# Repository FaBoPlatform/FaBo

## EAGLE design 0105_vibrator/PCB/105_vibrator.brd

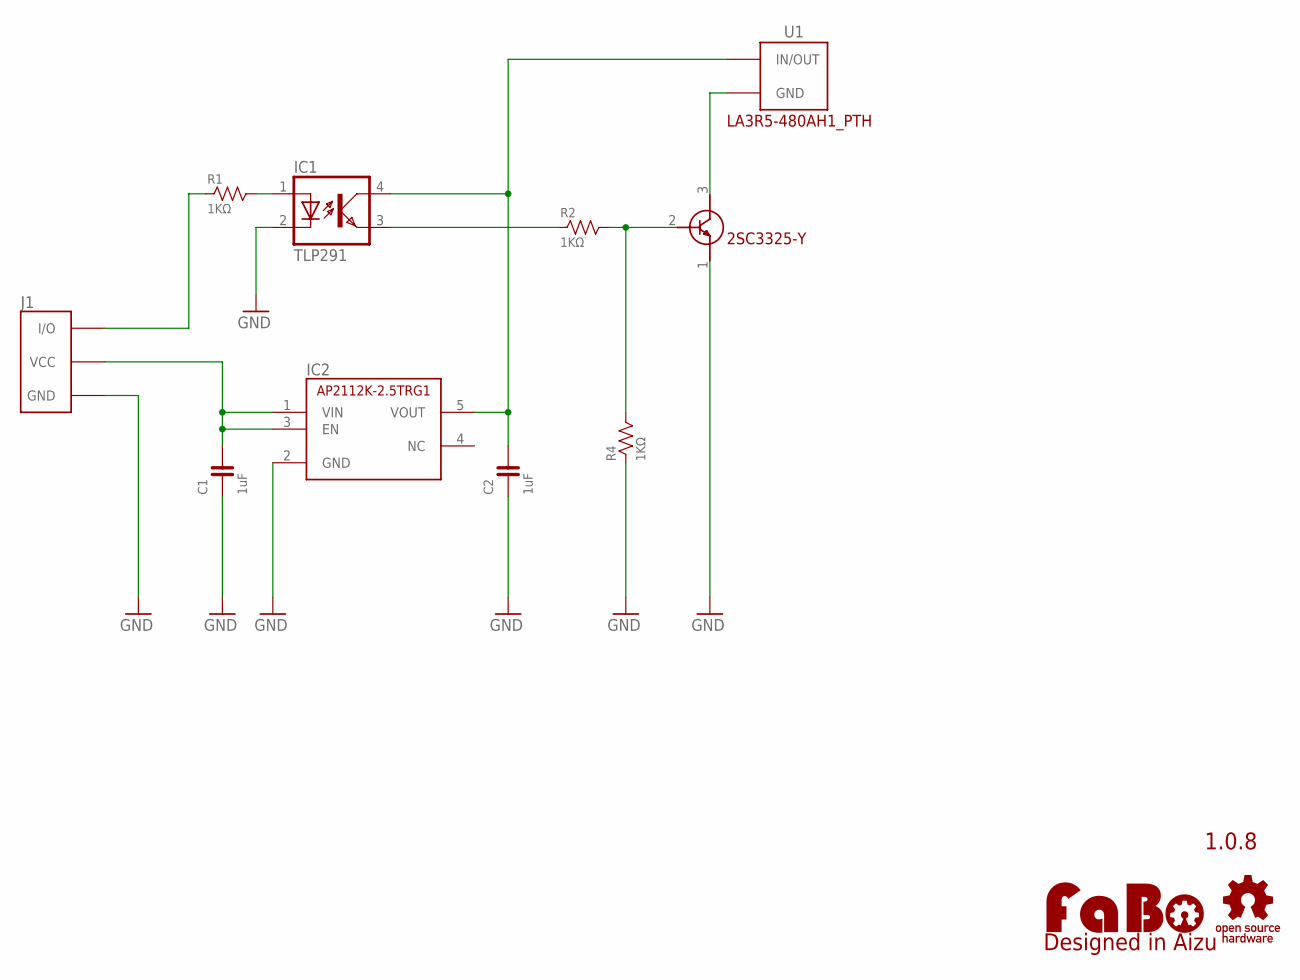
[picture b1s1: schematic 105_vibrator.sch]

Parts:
C1, C2: 1uF; 0603
IC1: TLP291; MINI-FLAT-4
IC2: AP2112-2.5; SOT-23-5
J1: FABO_BRICK_3PIN
LOGO1: LOGO_FABO-M; LOGO_FABO_M
R1, R2, R4: 1KΩ; 0603
TR1: 2SC3325-Y; SC-59
U1: VIBRATOR; LA3R5-480AH1_PTH
U$2: LOGO_OSHW-M_BOTTOM; LOGO_OSHW_M_BOTTOM

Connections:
GND: C1.1, C2.1, IC1.2 (C), IC2.2 (GND), J1.GND, R4.1, TR1.1 (E)
unnamed: J1.I/O, R1.1
unnamed: IC1.1 (A), R1.2
unnamed: IC1.3 (EMIT), R2.1
unnamed: C2.2, IC1.4 (COL), IC2.5 (VOUT), U1.P$1 (IN/OUT)
unnamed: TR1.3 (C), U1.P$2 (GND)
unnamed: R2.2, R4.2, TR1.2 (B)
VCC: C1.2, IC2.1 (VIN), IC2.3 (EN), J1.VCC

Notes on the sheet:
1.0.8
LA3R5-480AH1_PTH

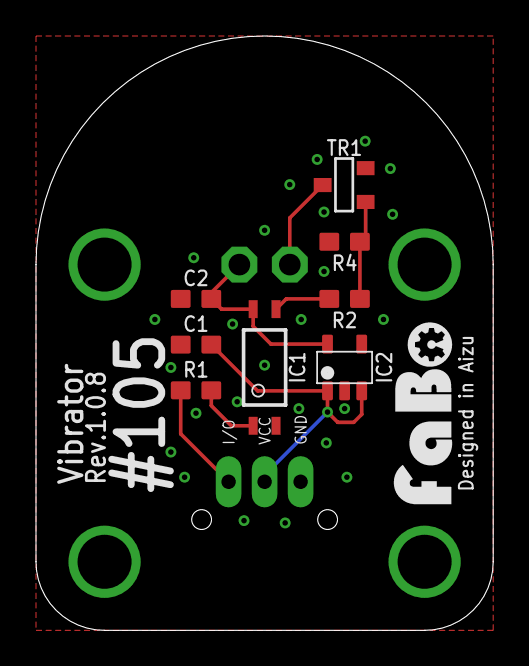
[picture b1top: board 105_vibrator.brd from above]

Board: 2 copper layers, 25.4 x 33.0 mm, 12 parts (0 on the bottom side), 8 nets.

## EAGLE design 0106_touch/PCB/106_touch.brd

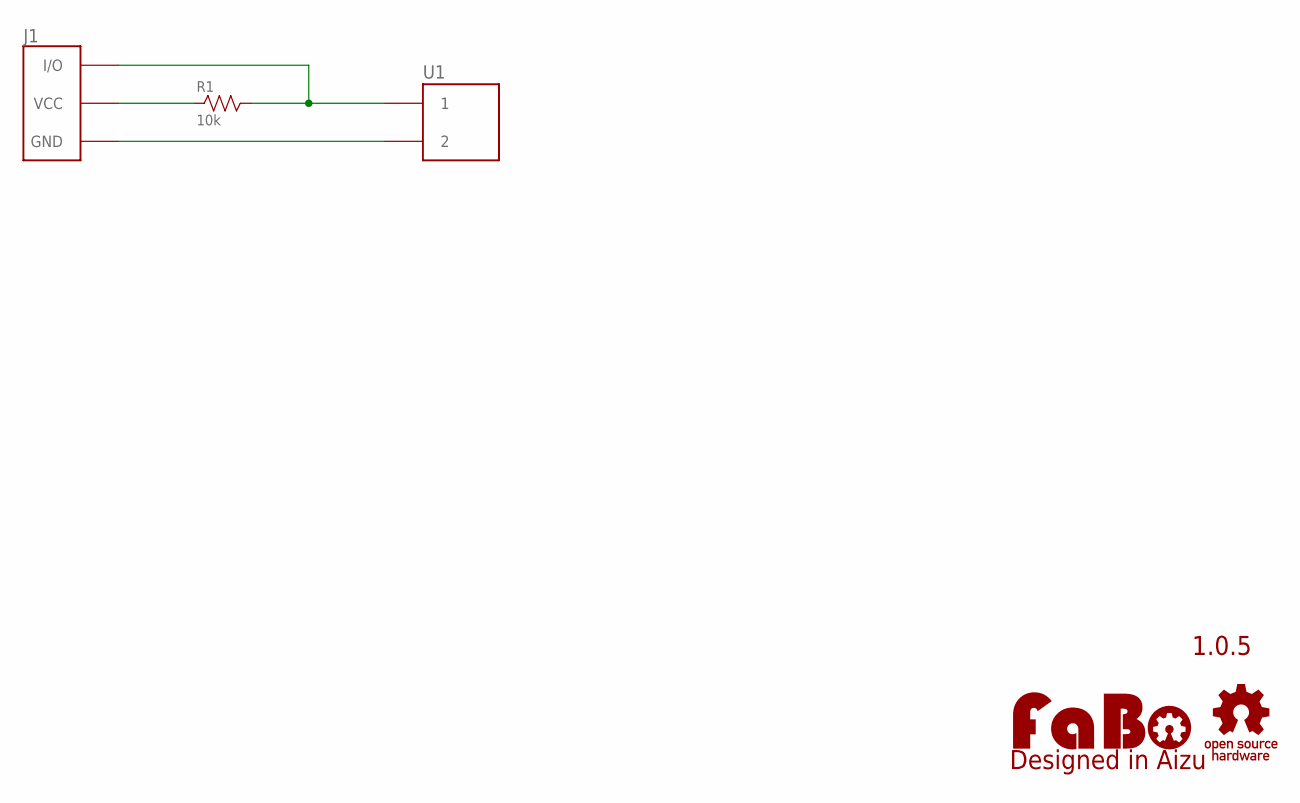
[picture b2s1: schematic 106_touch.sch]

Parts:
J1: FABO_BRICK_3PIN
LOGO1: LOGO_FABO-M; LOGO_FABO_M
R1: 10k; AXL-REGULAR
U1: FSR402-SHORT
U$2: LOGO_OSHW-M_BOTTOM; LOGO_OSHW_M_BOTTOM

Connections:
GND: J1.GND, U1.P$2 (2)
unnamed: J1.I/O, R1.2, U1.P$1 (1)
unnamed: J1.VCC, R1.1

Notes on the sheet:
1.0.5

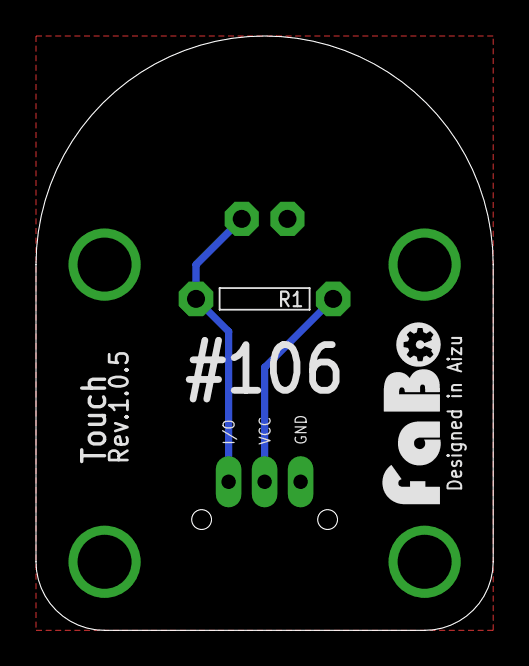
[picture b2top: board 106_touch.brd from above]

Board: 2 copper layers, 25.4 x 33.0 mm, 5 parts (0 on the bottom side), 3 nets.

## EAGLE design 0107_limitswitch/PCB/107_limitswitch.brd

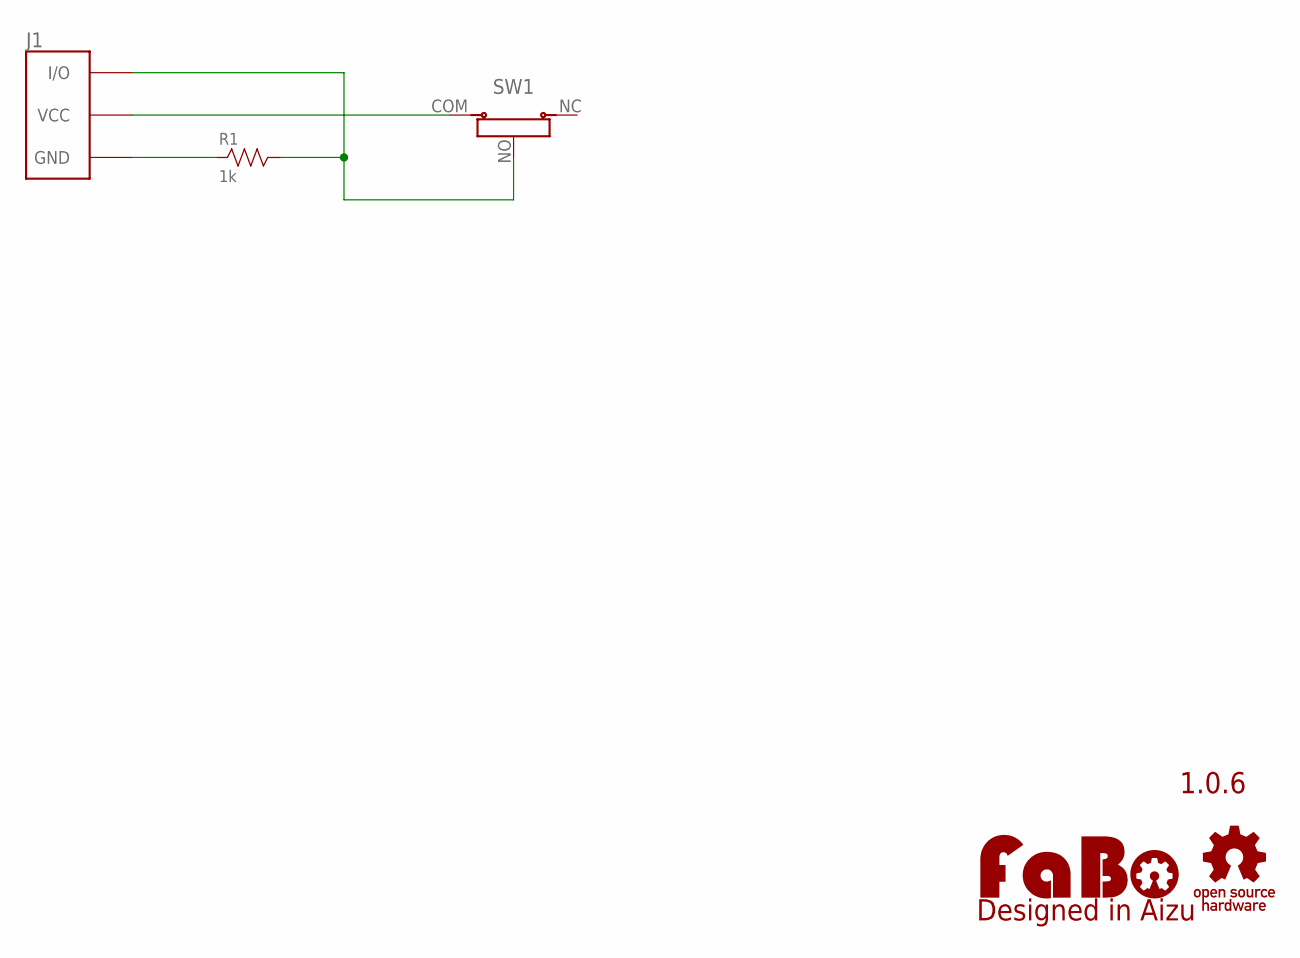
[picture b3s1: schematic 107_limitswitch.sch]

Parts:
J1: FABO_BRICK_3PIN
LOGO1: LOGO_FABO-M; LOGO_FABO_M
R1: 1k; AXL-REGULAR
SW1: LIMIT-SWITCH
U$2: LOGO_OSHW-M_BOTTOM; LOGO_OSHW_M_BOTTOM

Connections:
GND: J1.GND, R1.1
unnamed: J1.VCC, SW1.COM (VCC)
unnamed: J1.I/O, R1.2, SW1.NO

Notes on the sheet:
1.0.6

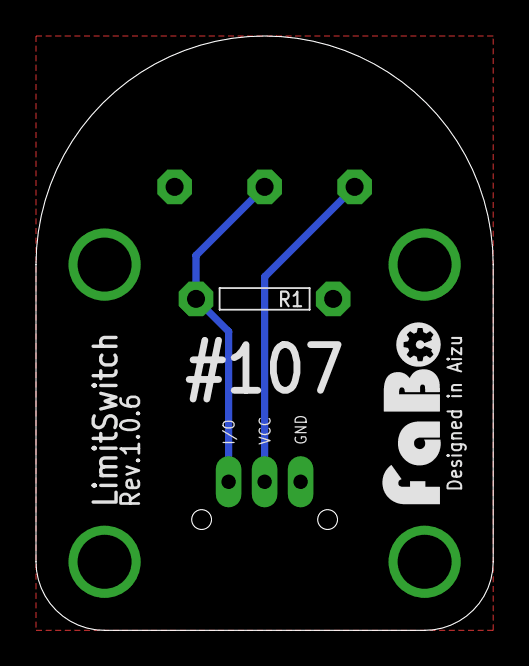
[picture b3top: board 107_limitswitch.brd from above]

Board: 2 copper layers, 25.4 x 33.0 mm, 5 parts (0 on the bottom side), 3 nets.

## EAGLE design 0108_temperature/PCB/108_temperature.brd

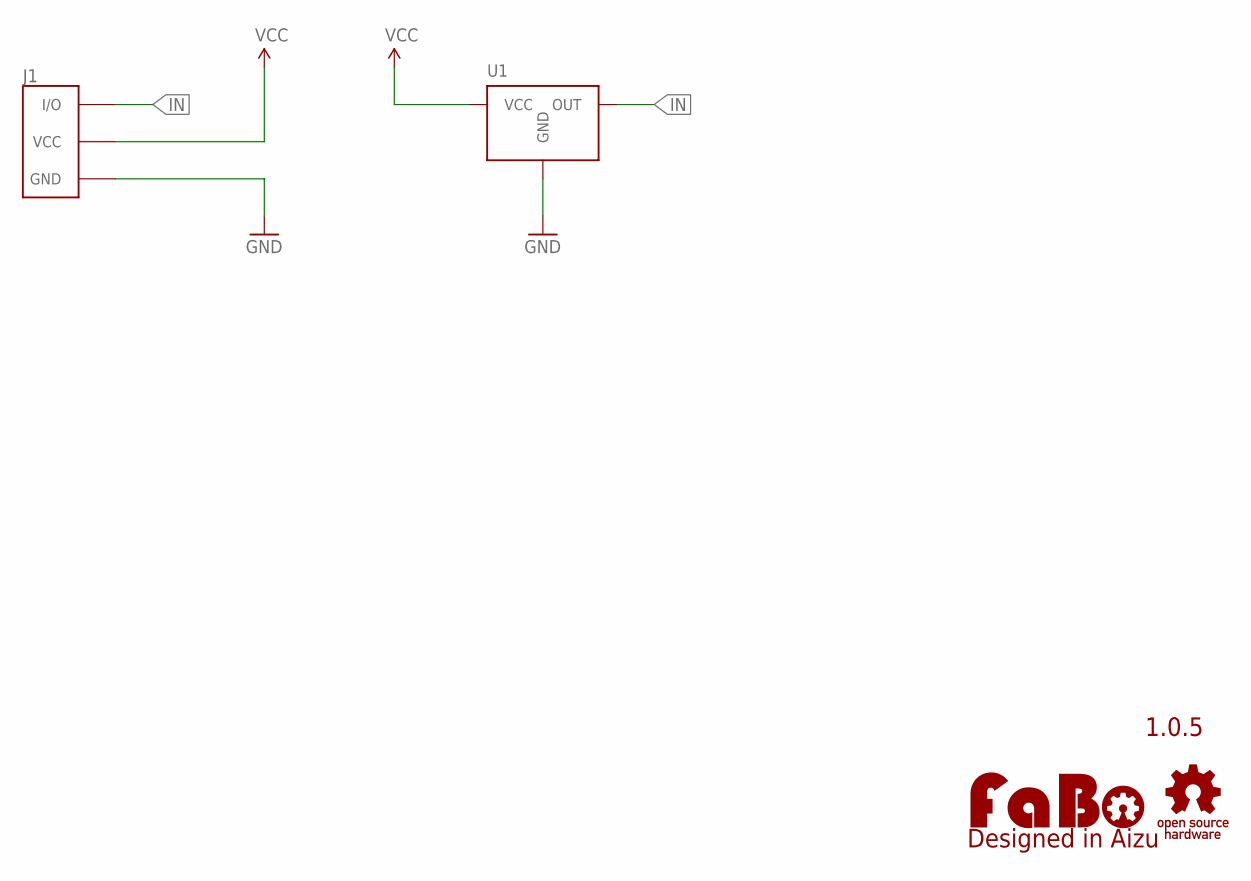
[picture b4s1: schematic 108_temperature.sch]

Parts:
J1: FABO_BRICK_3PIN
LOGO1: LOGO_FABO-M; LOGO_FABO_M
U1: LM61CIZ-TO-92; LM60-TO-92
U$2: LOGO_OSHW-M_BOTTOM; LOGO_OSHW_M_BOTTOM

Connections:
GND: J1.GND, U1.GND
IN: J1.I/O, U1.OUT
VCC: J1.VCC, U1.VCC

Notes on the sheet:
1.0.5

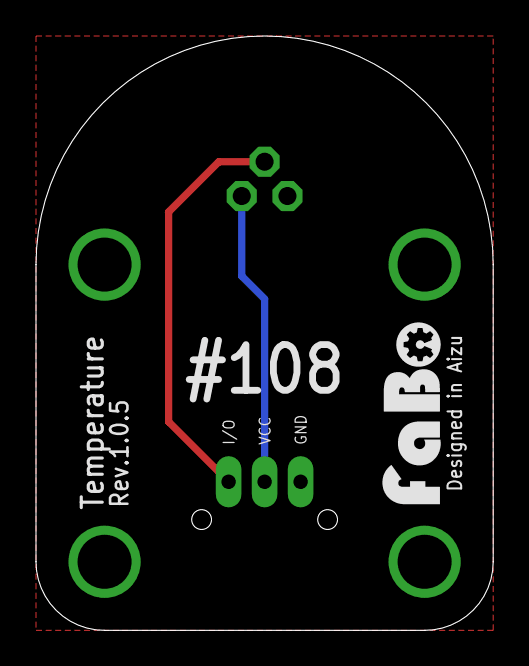
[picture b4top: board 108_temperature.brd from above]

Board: 2 copper layers, 25.4 x 33.0 mm, 4 parts (0 on the bottom side), 3 nets.

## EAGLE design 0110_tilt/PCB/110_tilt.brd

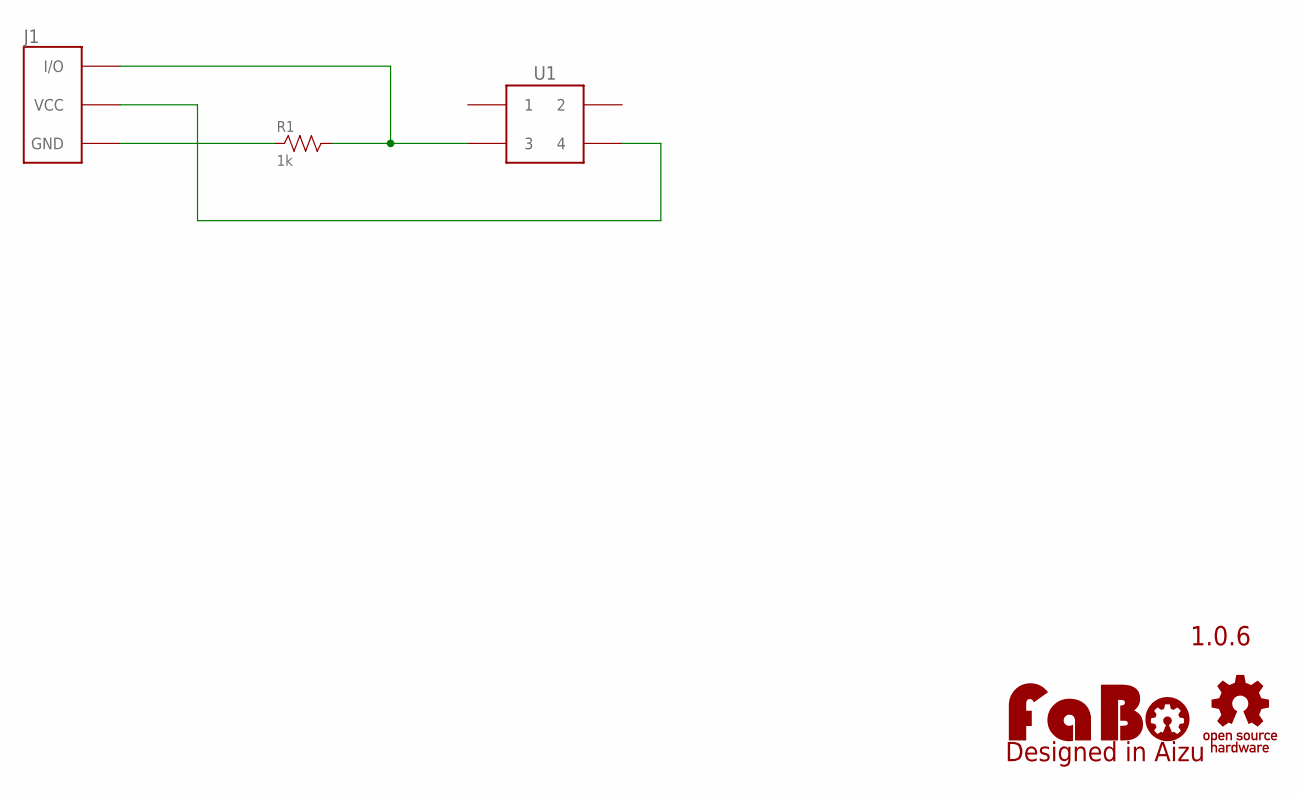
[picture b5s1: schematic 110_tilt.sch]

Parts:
J1: FABO_BRICK_3PIN
LOGO1: LOGO_FABO-M; LOGO_FABO_M
R1: 1k; AXL-REGULAR
U1: TILT; RBS040200
U$2: LOGO_OSHW-M_BOTTOM; LOGO_OSHW_M_BOTTOM

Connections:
GND: J1.GND, R1.1
unnamed: J1.I/O, R1.2, U1.3
unnamed: J1.VCC, U1.4

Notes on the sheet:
1.0.6

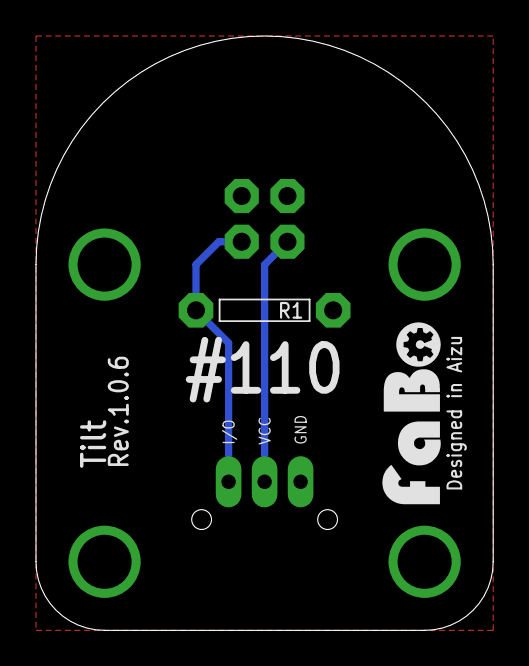
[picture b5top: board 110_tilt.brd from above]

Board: 2 copper layers, 25.4 x 33.0 mm, 5 parts (0 on the bottom side), 3 nets.

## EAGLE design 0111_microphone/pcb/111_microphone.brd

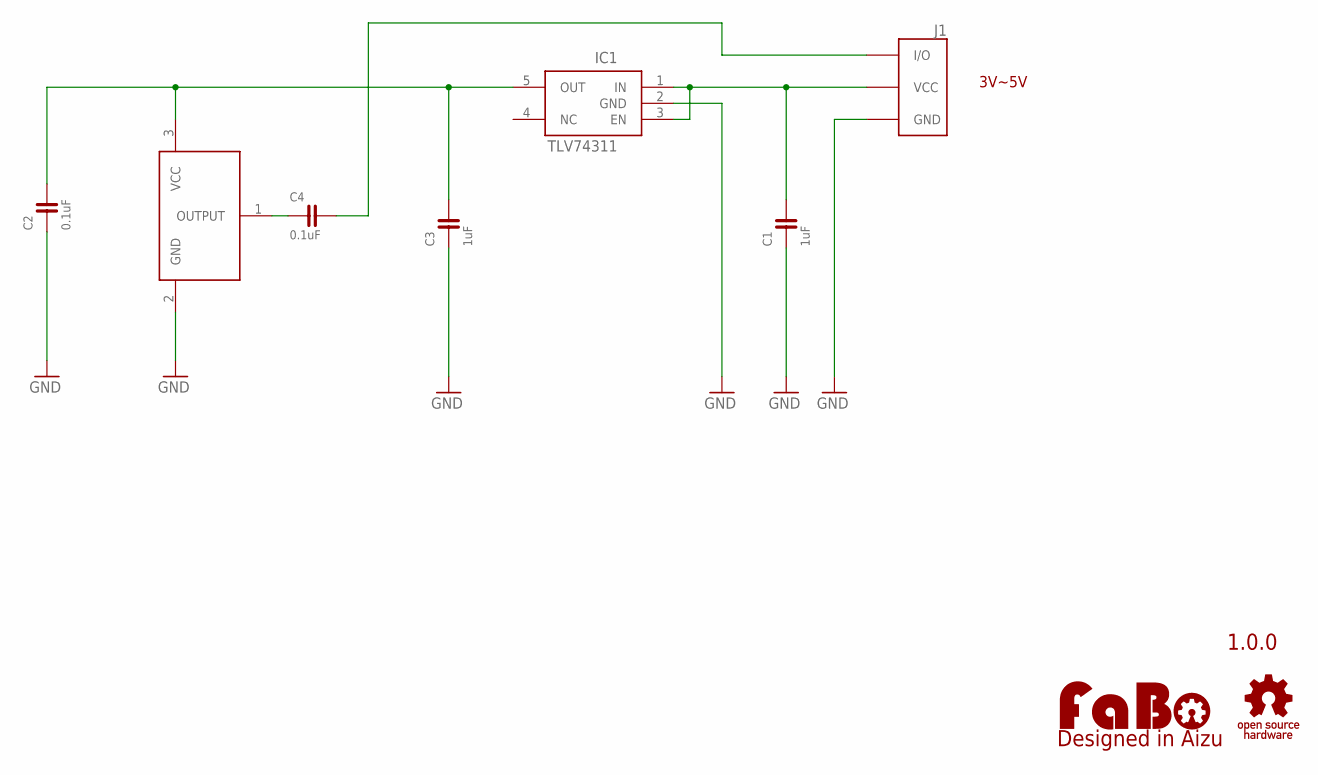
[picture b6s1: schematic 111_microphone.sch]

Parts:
C1, C3: 1uF; 0603
C2, C4: 0.1uF; 0603
IC1: TLV74311; SOT-23-5
ICS40310: ANALOG-MICICS40310; ICS40310
J1: FABO_BRICK_3PIN-03B-PASK-1_NAME_BOTTOM; FABO_BRICK_3PIN_B03B-PASK-1_NAME_BOTTOM
LOGO1: LOGO_FABO-S_BOTTOM; LOGO_FABO_S_BOTTOM
U$3: LOGO_OSHW-S_BOTTOM; LOGO_OSHW_S_BOTTOM

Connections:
GND: C1.1, C2.1, C3.1, IC1.2 (GND), ICS40310.2 (GND), J1.GND
unnamed: C1.2, IC1.1 (IN), IC1.3 (EN), J1.VCC
unnamed: C2.2, C3.2, IC1.5 (OUT), ICS40310.3 (VCC)
unnamed: C4.2, J1.I/O
unnamed: C4.1, ICS40310.1 (OUTPUT)

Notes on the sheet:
3V~5V
1.0.0

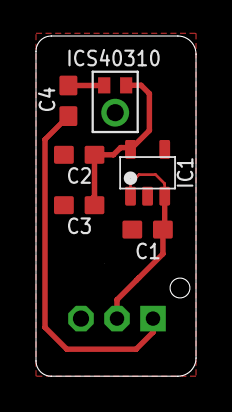
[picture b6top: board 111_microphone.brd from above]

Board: 2 copper layers, 8.9 x 18.9 mm, 9 parts (0 on the bottom side), 5 nets.

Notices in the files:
parts and their libraries:
FaBo-etc: Released under the Creative Commons Attribution-ShareAlike 4.0 License
https://creativecommons.org/licenses/by-sa/4.0
FaBo-etc: Released under the Creative Commons
